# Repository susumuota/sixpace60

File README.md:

# Infinite Monkey Sixpace60

- Based on 60% layout
- Six space keys
- Arrow keys
- No stabilizers
- Supports [VIA](https://caniusevia.com/), [Remap](https://remap-keys.app/) and [VIAL](https://get.vial.today/)

## Installation

- Install [QMK Toolbox](https://qmk.fm/toolbox) to flash the firmware
- Open the QMK Toolbox
- Connect your keyboard
- Press `Open` and select the firmware file [firmware/infinitemonkey_sixpace60_via.hex](firmware/infinitemonkey_sixpace60_via.hex) for VIA or [firmware/infinitemonkey_sixpace60_vial.hex](firmware/infinitemonkey_sixpace60_vial.hex) for VIAL
- Press the reset button on your keyboard **twice quickly** to put it into bootloader mode
- Press `Flash` in the QMK Toolbox

## Setting Up with VIA

- Go to [VIA](https://www.usevia.app/)
- Press `SETTINGS` and turn on `Show Design tab`
- Press `DESIGN`, press `Load`, and select [qmk/keyboards/infinitemonkey/sixpace60/via.json](qmk/keyboards/infinitemonkey/sixpace60/via.json)
- Press `CONFIGURE` press `Authorize device +` and select `Sixpace60`

## Setting Up with VIAL

- Go to [Vial Web](https://vial.rocks/)
- Press `Start Vial`
- Select `Sixpace60`

## Building the Firmware

Install [Docker](https://www.docker.com/get-started) to build the firmware.

### Build for VIA and Remap

```shell
git clone https://github.com/qmk/qmk_firmware.git
git clone https://github.com/susumuota/sixpace60.git
cp -rp sixpace60/qmk/keyboards/infinitemonkey qmk_firmware/keyboards
cd qmk_firmware
RUNTIME="docker" SKIP_FLASHING_SUPPORT=1 util/docker_cmd.sh make infinitemonkey/sixpace60:via
```

### Build for VIAL

```shell
git clone https://github.com/vial-kb/vial-qmk.git
git clone https://github.com/susumuota/sixpace60.git
cp -rp sixpace60/qmk/keyboards/infinitemonkey vial-qmk/keyboards
cd vial-qmk
RUNTIME="docker" SKIP_FLASHING_SUPPORT=1 util/docker_cmd.sh make infinitemonkey/sixpace60:vial
```

## License

This project is licensed under the MIT License - see the [LICENSE](LICENSE) file for details.

## Author

- [Susumu OTA](https://github.com/susumuota)

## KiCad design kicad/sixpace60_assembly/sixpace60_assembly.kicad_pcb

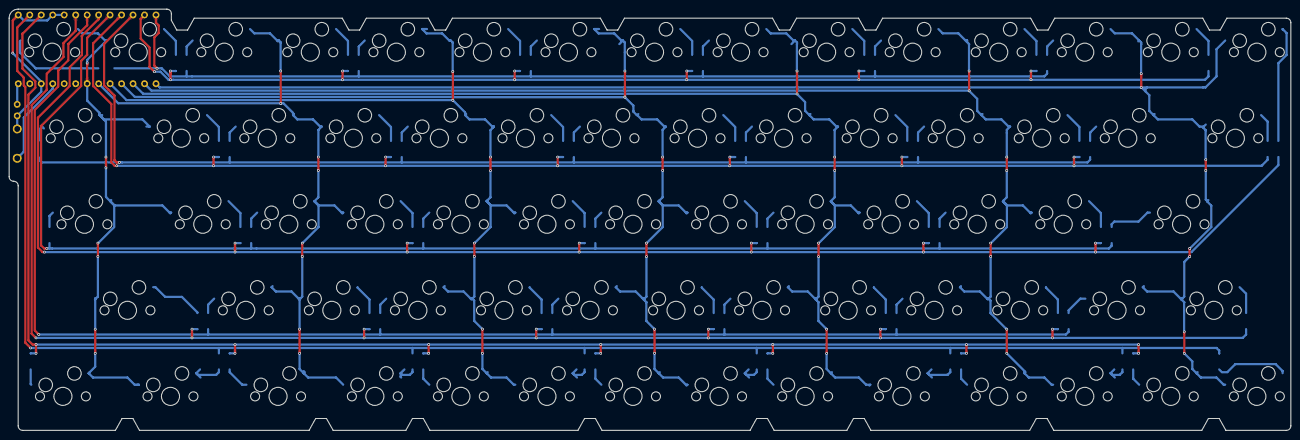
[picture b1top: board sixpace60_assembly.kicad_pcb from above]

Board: 2 copper layers, 283.8 x 93.3 mm, 141 parts (1 on the bottom side), 89 nets.

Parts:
D1, D2, D3, D4, D5, D6, D7, D8, D9, D10, D11, D12, D13, D14, D15, D16, D17, D18, D19, D20, D21, D22, D23, D24, D25, D26, D27, D28, D29, D30, D31, D32, D33, D34, D35, D36, D37, D38, D39, D40, D41, D42, D43, D44, D45, D46, D47, D48, D49, D50, D51, D52, D53, D54, D55, D56, D57, D58, D59, D60, D61, D62, D63, D64, D65, D66, D67, D68, D69: D; Diode_SMD
J1: Conn_01x02; Battery_BMP_2pin
SW1, SW5, SW6, SW7, SW10, SW11, SW12, SW13, SW15, SW16, SW17, SW18, SW19, SW20, SW21, SW22, SW23, SW24, SW25, SW26, SW27, SW28, SW29, SW30, SW31, SW32, SW33, SW34, SW35, SW36, SW37, SW38, SW39, SW40, SW41, SW42, SW43, SW44, SW45, SW46, SW47, SW48, SW50, SW51, SW52, SW53, SW54, SW55, SW56, SW57, SW58, SW59, SW60, SW61, SW64, SW65, SW67, SW68, SW69: SW_Push; CherryMX_Hotswap_1u_Small3
SW2, SW66: SW_Push; CherryMX_Hotswap_1.5u
SW3, SW8, SW62: SW_Push; CherryMX_Hotswap_1.75u
SW4, SW9, SW14, SW49, SW63: SW_Push; CherryMX_Hotswap_1.25u
SW70: SW_Push; ResetSW
U1: Micon_BLEMicroPro; Micon_BMP_7sKB

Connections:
Bat+: J1.1, U1.25 (BAT+)
Col0: SW1.2, SW2.2, SW3.2, SW4.2, SW5.1, SW6.1, SW7.1, SW8.1, SW9.1, U1.19 (F5/PIN19)
Col1: SW10.2, SW11.2, SW12.2, SW13.2, SW14.2, SW15.1, SW16.1, SW17.1, SW18.1, SW19.1, U1.18 (F6/PIN18)
Col2: SW20.2, SW21.2, SW22.2, SW23.2, SW24.2, SW25.1, SW26.1, SW27.1, SW28.1, SW29.1, U1.17 (F7/PIN17)
Col3: SW30.2, SW31.2, SW32.2, SW33.2, SW34.2, SW35.1, SW36.1, SW37.1, SW38.1, SW39.1, U1.16 (B1/PIN16)
Col4: SW40.2, SW41.2, SW42.2, SW43.2, SW44.2, SW45.1, SW46.1, SW47.1, SW48.1, SW49.1, U1.15 (B3/PIN15)
Col5: SW50.2, SW51.2, SW52.2, SW53.2, SW54.2, SW55.1, SW56.1, SW57.1, SW58.1, SW59.1, U1.14 (B2/PIN14)
Col6: SW60.2, SW61.2, SW62.2, SW63.2, SW64.2, SW65.1, SW66.1, SW67.1, SW68.1, SW69.1, U1.13 (B6/PIN13)
GND: J1.2, SW70.2, U1.3 (GND), U1.4 (GND), U1.23 (GND), U1.26 (BAT-)
unnamed: D1.2 (A), SW1.1
unnamed: D2.2 (A), SW2.1
unnamed: D3.2 (A), SW3.1
unnamed: D4.2 (A), SW4.1
unnamed: D5.2 (A), SW5.2
unnamed: D6.2 (A), SW6.2
unnamed: D7.2 (A), SW7.2
unnamed: D8.2 (A), SW8.2
unnamed: D9.2 (A), SW9.2
unnamed: D10.2 (A), SW10.1
unnamed: D11.2 (A), SW11.1
unnamed: D12.2 (A), SW12.1
unnamed: D13.2 (A), SW13.1
unnamed: D14.2 (A), SW14.1
unnamed: D15.2 (A), SW15.2
unnamed: D16.2 (A), SW16.2
unnamed: D17.2 (A), SW17.2
unnamed: D18.2 (A), SW18.2
unnamed: D19.2 (A), SW19.2
unnamed: D20.2 (A), SW20.1
unnamed: D21.2 (A), SW21.1
unnamed: D22.2 (A), SW22.1
unnamed: D23.2 (A), SW23.1
unnamed: D24.2 (A), SW24.1
unnamed: D25.2 (A), SW25.2
unnamed: D26.2 (A), SW26.2
unnamed: D27.2 (A), SW27.2
unnamed: D28.2 (A), SW28.2
unnamed: D29.2 (A), SW29.2
unnamed: D30.2 (A), SW30.1
unnamed: D31.2 (A), SW31.1
unnamed: D32.2 (A), SW32.1
unnamed: D33.2 (A), SW33.1
unnamed: D34.2 (A), SW34.1
unnamed: D35.2 (A), SW35.2
unnamed: D36.2 (A), SW36.2
unnamed: D37.2 (A), SW37.2
unnamed: D38.2 (A), SW38.2
unnamed: D39.2 (A), SW39.2
unnamed: D40.2 (A), SW40.1
unnamed: D41.2 (A), SW41.1
unnamed: D42.2 (A), SW42.1
unnamed: D43.2 (A), SW43.1
unnamed: D44.2 (A), SW44.1
unnamed: D45.2 (A), SW45.2
unnamed: D46.2 (A), SW46.2
unnamed: D47.2 (A), SW47.2
unnamed: D48.2 (A), SW48.2
unnamed: D49.2 (A), SW49.2
unnamed: D50.2 (A), SW50.1
unnamed: D51.2 (A), SW51.1
unnamed: D52.2 (A), SW52.1
unnamed: D53.2 (A), SW53.1
unnamed: D54.2 (A), SW54.1
unnamed: D55.2 (A), SW55.2
unnamed: D56.2 (A), SW56.2
unnamed: D57.2 (A), SW57.2
unnamed: D58.2 (A), SW58.2
unnamed: D59.2 (A), SW59.2
unnamed: D60.2 (A), SW60.1
unnamed: D61.2 (A), SW61.1
unnamed: D62.2 (A), SW62.1
unnamed: D63.2 (A), SW63.1
unnamed: D64.2 (A), SW64.1
unnamed: D65.2 (A), SW65.2
unnamed: D66.2 (A), SW66.2
unnamed: D67.2 (A), SW67.2
unnamed: D68.2 (A), SW68.2
unnamed: D69.2 (A), SW69.2
Reset: SW70.1, U1.22 (RST)
Row0: D1.1 (K), D10.1 (K), D20.1 (K), D30.1 (K), D40.1 (K), D50.1 (K), D60.1 (K), U1.12 (B5/PIN12)
Row1: D5.1 (K), D15.1 (K), D25.1 (K), D35.1 (K), D45.1 (K), D55.1 (K), D65.1 (K), U1.11 (B4/PIN11)
Row2: D2.1 (K), D11.1 (K), D21.1 (K), D31.1 (K), D41.1 (K), D51.1 (K), D61.1 (K), U1.10 (E6/PIN10)
Row3: D6.1 (K), D16.1 (K), D26.1 (K), D36.1 (K), D46.1 (K), D56.1 (K), D66.1 (K), U1.9 (D7/PIN9)
Row4: D3.1 (K), D12.1 (K), D22.1 (K), D32.1 (K), D42.1 (K), D52.1 (K), D62.1 (K), U1.8 (C6/PIN8)
Row5: D7.1 (K), D17.1 (K), D27.1 (K), D37.1 (K), D47.1 (K), D57.1 (K), D69.1 (K), U1.7 (D4/PIN7)
Row6: D13.1 (K), D23.1 (K), D33.1 (K), D43.1 (K), D53.1 (K), D63.1 (K), U1.6 (D0/PIN6/SCL)
Row7: D8.1 (K), D18.1 (K), D28.1 (K), D38.1 (K), D48.1 (K), D58.1 (K), D67.1 (K), U1.5 (D1/PIN5/SDA)
Row8: D4.1 (K), D14.1 (K), D24.1 (K), D34.1 (K), D44.1 (K), D54.1 (K), D64.1 (K), U1.2 (D2/PIN2)
Row9: D9.1 (K), D19.1 (K), D29.1 (K), D39.1 (K), D49.1 (K), D59.1 (K), D68.1 (K), U1.1 (D3/PIN1)

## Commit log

2025-06-08 feat: Sixpace60 v1.0.0
2025-06-17 docs: add images
2025-06-17 feat: add firmwares
2025-06-17 docs: fix link
